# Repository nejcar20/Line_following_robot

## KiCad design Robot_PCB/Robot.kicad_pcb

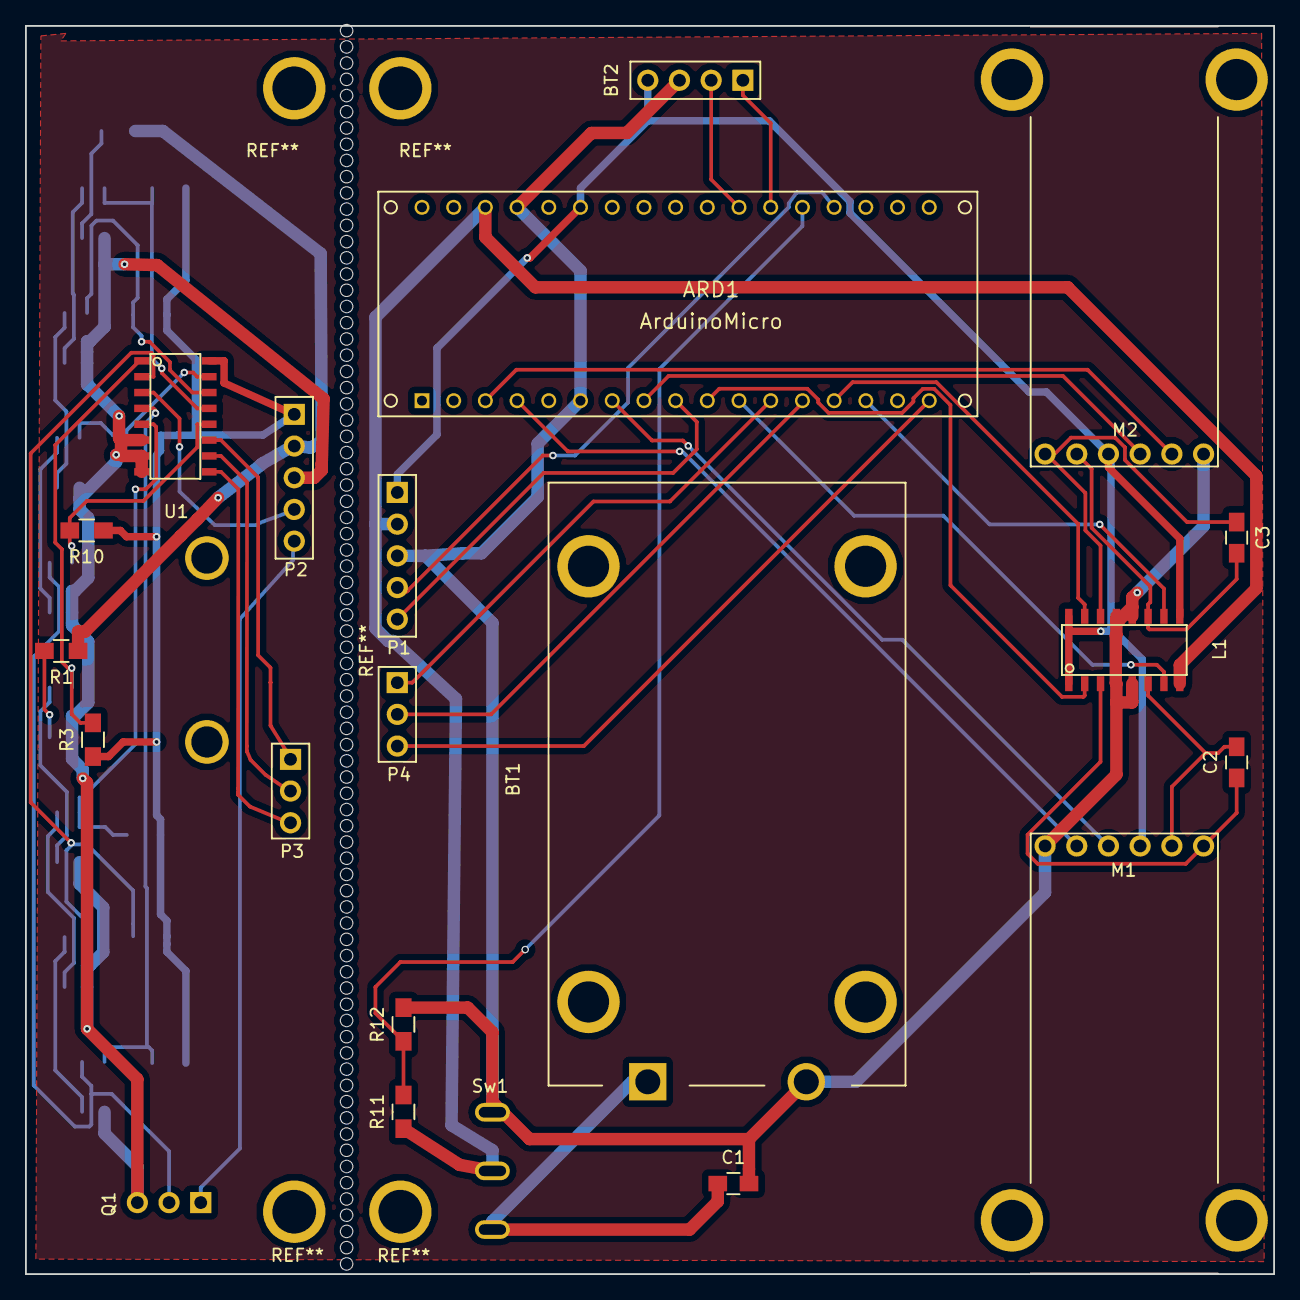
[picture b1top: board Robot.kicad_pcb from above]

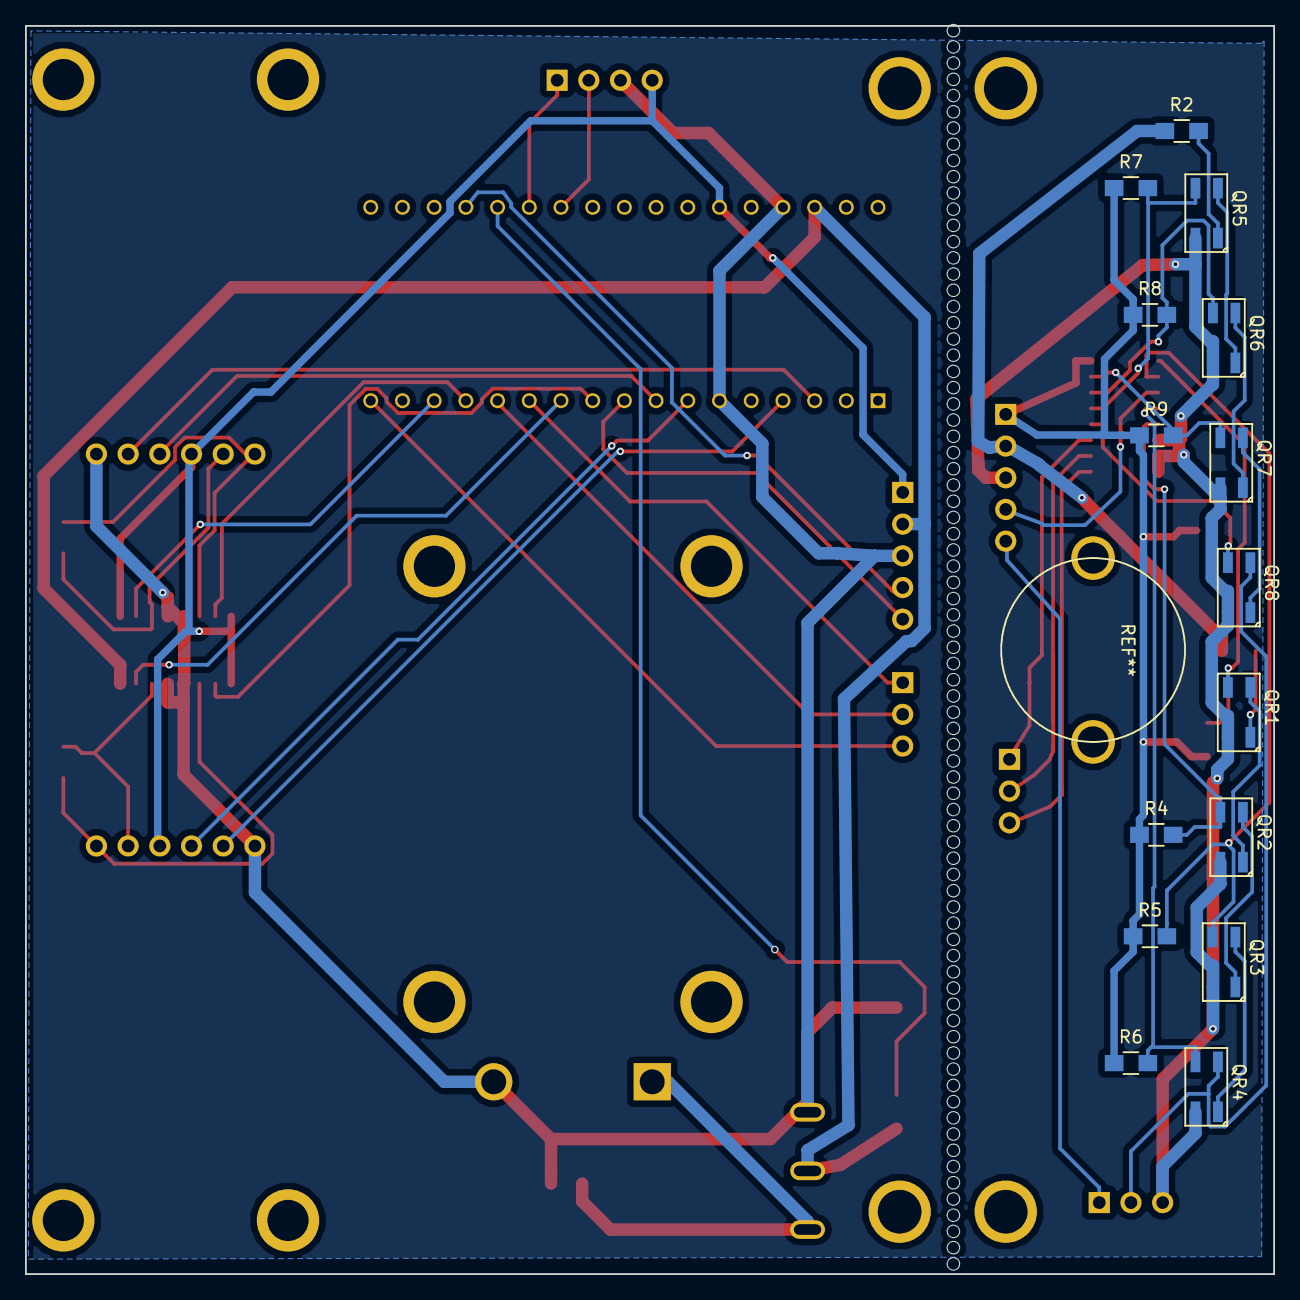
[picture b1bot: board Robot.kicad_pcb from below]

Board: 2 copper layers, 100.0 x 100.0 mm, 36 parts (15 on the bottom side), 41 nets.

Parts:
ARD1: ArduinoMicro; ARDUINO_MICRO_SHIELD
BT1: Battery_Cell; battery_holder_1291
BT2: JY-MCU
C1, C2, C3: 22uF; C_0805_HandSoldering
L1: L293; Multiplexer_74HCT4051_SO16
M1: LMotor; EM_holder
M2: RMotor; EM_holder
P1, P2: CONN_01X05; CONN_5x1
P3, P4: CONN_01X03; Conn_01x03
Q1: Q_NPN_BCE; NPN_transistor
QR1, QR2, QR3, QR4, QR5, QR6, QR7, QR8: QRE1113; QRE1113GR
R1, R2: 150; R_0805_HandSoldering
R3, R4, R5, R6, R7, R8, R9, R10, R11, R12: 10k; R_0805_HandSoldering
Sw1: Switch; Switch_toggle
U1: 74HCT4051; Multiplexer_74HCT4051_SO16

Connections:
+5V: ARD1.29, BT2.4, L1.1, L1.9, L1.16, M1.3, M2.3, P1.1, P2.1, R3.1, R4.1, R5.1, R6.1, R7.1, R8.1, R9.1, R10.1, U1.16
+9V: ARD1.32, L1.8, P1.2, P2.2, R1.1, R2.1, R11.1, Sw1.2
Batt: ARD1.22, R11.2, R12.1
D_on: ARD1.9, P1.5, P2.5, Q1.1
EncLA: ARD1.7, M1.4
EncLB: ARD1.4, M1.5
EncRA: ARD1.8, M2.4
EncRB: ARD1.3, M2.5
GND: ARD1.6, ARD1.31, BT1.2, BT2.3, C1.2, L1.4, L1.5, L1.12, L1.13, M1.6, M2.6, P1.3, P2.3, Q1.3, QR1.4, QR2.4, QR3.4, QR4.4, QR5.4, QR6.4, QR7.4, QR8.4, R12.2, Sw1.3, U1.6, U1.7, U1.8
Mux: ARD1.21, P1.4, P2.4, U1.3
unnamed: ARD1.23, BT2.1
unnamed: ARD1.24, BT2.2
unnamed: BT1.1, C1.1, Sw1.1
unnamed: C2.1, L1.3, M1.1
unnamed: C2.2, L1.6, M1.2
unnamed: C3.1, L1.14, M2.1
unnamed: C3.2, L1.11, M2.2
unnamed: Q1.2, QR4.2, QR8.2
unnamed: QR1.1, R1.2
unnamed: QR1.2, QR2.1
unnamed: QR1.3, R3.2, U1.1
unnamed: QR2.2, QR3.1
unnamed: QR2.3, R4.2, U1.5
unnamed: QR3.2, QR4.1
unnamed: QR3.3, R5.2, U1.2
unnamed: QR4.3, R6.2, U1.4
unnamed: QR5.1, R2.2
unnamed: QR5.2, QR6.1
unnamed: QR5.3, R7.2, U1.13
unnamed: QR6.2, QR7.1
unnamed: QR6.3, R8.2, U1.14
unnamed: QR7.2, QR8.1
unnamed: QR7.3, R9.2, U1.15
unnamed: QR8.3, R10.2, U1.12
PWML1: ARD1.10, L1.2
PWML2: ARD1.11, L1.7
PWMR1: ARD1.15, L1.10
PWMR2: ARD1.14, L1.15
S0: ARD1.12, P3.1, P4.1, U1.11
S1: ARD1.13, P3.2, P4.2, U1.10
S2: ARD1.17, P3.3, P4.3, U1.9

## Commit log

2017-02-27 :octocat: Added .gitattributes & .gitignore files
2017-02-27 Vaja_KiCAD
2017-03-12 Robot
    Shema robota kiCAD in pdf
